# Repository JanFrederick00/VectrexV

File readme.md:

# Vectrex-V

This device can generate a vector signal that can be displayed as X/Y on an oscilloscope or vector monitor.

The DACs used are MCP4811-devices featuring a built-in voltage reference, giving a stable output with a 10-bit range.

The DACs are connected to a CH32V003 microcontroller running at 48MHz. In practice the maximum output frequency on the DACs is about 60KHz, minus the time needed for calculations.

A third output channel is provided (Z) to control the beam brightness (on/off), which eliminates faint line when "jumping" from one position to another.

A simple 2-channel pulse wave audio output is provided.

A controller header can be used to connect a SNES/NES controller or potentially other styles of controllers, provided they use no more than 3 I/O pins.

# Firmware

Firmware is written in c++ (Arduino / PlatformIO). 

## Asteroids

As a proof-of-concept I implemented my own version of the classic Atari game "Asteroids". It is not meant to be a faithful recreation of the original, even though it re-uses the graphics from the Atari version.
This program uses more than 98% of the CH32's flash memory (for game code and graphics data), and thus is probably a good representation of the capabilities of this device.

## Pong

A simple variation on a pong-like game, with (optional) gravity for the ball.

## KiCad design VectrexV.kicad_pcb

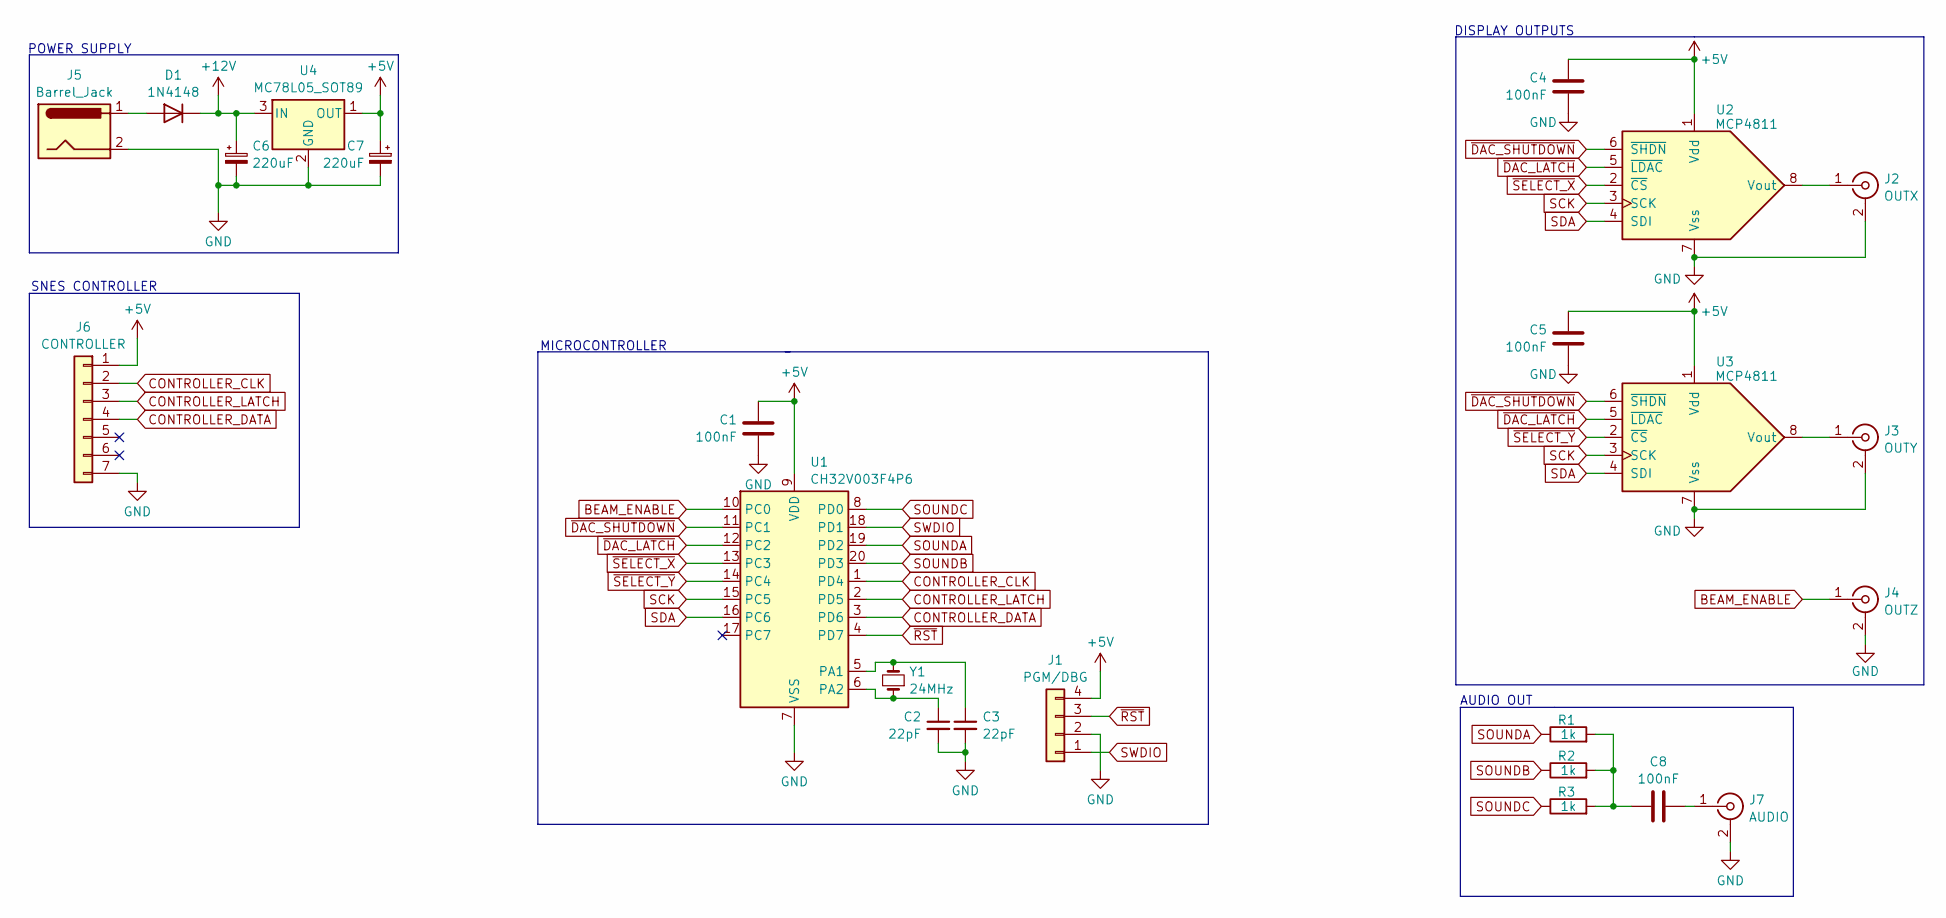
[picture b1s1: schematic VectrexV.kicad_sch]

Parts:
C1, C4, C5, C8: 100nF; C_0805_2012Metric_Pad1.18x1.45mm_HandSolder
C2, C3: 22pF; C_0805_2012Metric_Pad1.18x1.45mm_HandSolder
C6, C7: 220uF; CP_Radial_D5.0mm_P2.50mm
D1: 1N4148; D_DO-35_SOD27_P7.62mm_Horizontal
J1: PGM/DBG; PinHeader_1x04_P2.54mm_Vertical
J2: OUTX; RCA-jack
J3: OUTY; RCA-jack
J4: OUTZ; RCA-jack
J5: Barrel_Jack; BarrelJack_Horizontal
J6: CONTROLLER; PinHeader_1x07_P2.54mm_Vertical
J7: AUDIO; RCA-jack
R1, R2, R3: 1k; R_0805_2012Metric_Pad1.20x1.40mm_HandSolder
U1: CH32V003F4P6; TSSOP-20_4.4x6.5mm_P0.65mm
U2, U3: MCP4811; MSOP-8_3x3mm_P0.65mm
U4: MC78L05_SOT89; SOT-89-3
Y1: 24MHz; Crystal_HC50_Vertical

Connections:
+5V: C1.1, C4.1, C5.1, C7.1, J1.4, J6.1, U1.9 (VDD), U2.1 (Vdd), U3.1 (Vdd), U4.1 (OUT)
+12V: C6.1, D1.1 (K), U4.3 (IN)
BEAM_ENABLE: J4.1 (In), U1.10 (PC0)
CONTROLLER_CLK: J6.2, U1.1 (PD4)
CONTROLLER_DATA: J6.4, U1.3 (PD6)
CONTROLLER_LATCH: J6.3, U1.2 (PD5)
GND: C1.2, C2.2, C3.2, C4.2, C5.2, C6.2, C7.2, J1.2, J2.2 (Ext), J3.2 (Ext), J4.2 (Ext), J5.2, J6.7, J7.2 (Ext), U1.7 (VSS), U2.7 (Vss), U3.7 (Vss), U4.2 (GND)
unnamed: C8.1, R1.2, R2.2, R3.2
unnamed: D1.2 (A), J5.1
unnamed: J2.1 (In), U2.8 (Vout)
unnamed: J3.1 (In), U3.8 (Vout)
unnamed: C8.2, J7.1 (In)
unnamed: C3.1, U1.5 (PA1), Y1.2
unnamed: C2.1, U1.6 (PA2), Y1.1
SCK: U1.15 (PC5), U2.3 (SCK), U3.3 (SCK)
SDA: U1.16 (PC6), U2.4 (SDI), U3.4 (SDI)
SOUNDA: R1.1, U1.19 (PD2)
SOUNDB: R2.1, U1.20 (PD3)
SOUNDC: R3.1, U1.8 (PD0)
SWDIO: J1.1, U1.18 (PD1)
~DAC_LATCH: U1.12 (PC2), U2.5 (~LDAC), U3.5 (~LDAC)
~DAC_SHUTDOWN: U1.11 (PC1), U2.6 (~SHDN), U3.6 (~SHDN)
~RST: J1.3, U1.4 (PD7)
~SELECT_X: U1.13 (PC3), U2.2 (~CS)
~SELECT_Y: U1.14 (PC4), U3.2 (~CS)

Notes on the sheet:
POWER SUPPLY
MICROCONTROLLER
SNES CONTROLLER
AUDIO OUT
DISPLAY OUTPUTS

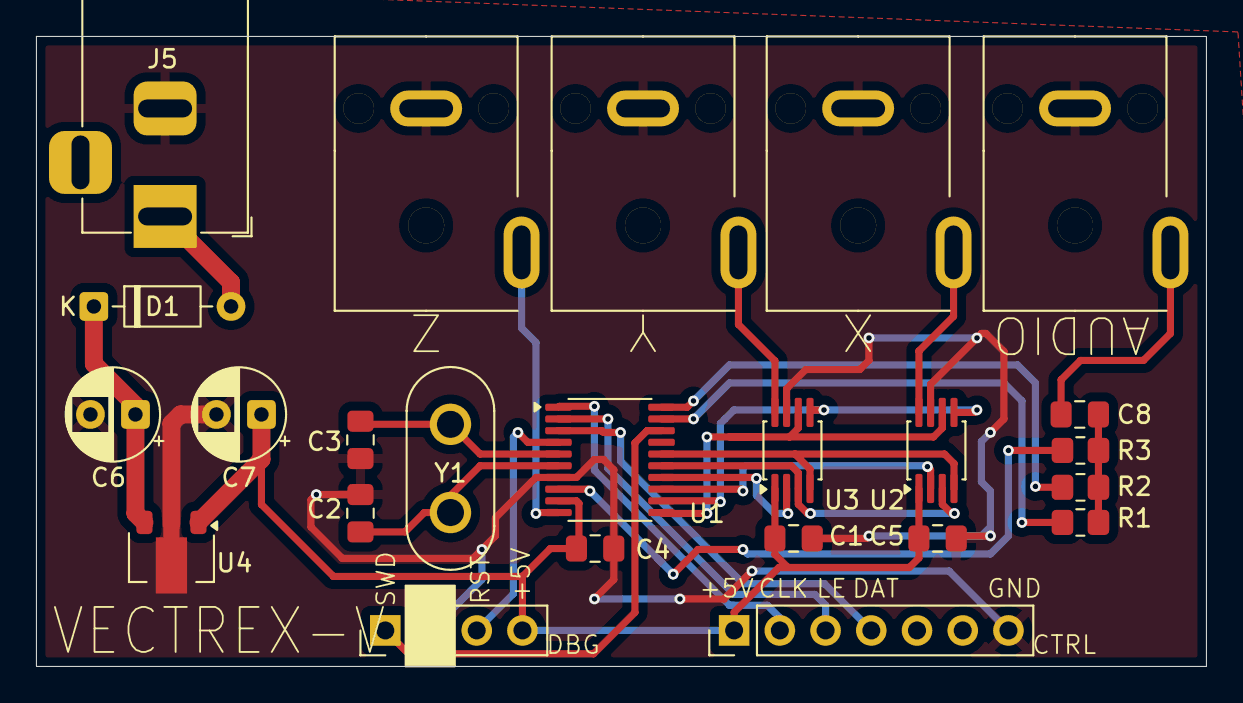
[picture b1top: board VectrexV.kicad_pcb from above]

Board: 2 copper layers, 65.0 x 35.0 mm, 24 parts (0 on the bottom side), 25 nets.

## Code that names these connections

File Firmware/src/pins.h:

#pragma once
#include <Arduino.h>

const uint8_t PIN_BRIGHTNESS = PC0;

// DACs
const uint8_t PIN_DAC_SHUTDOWN = PC1;
const uint8_t PIN_DAC_LATCH = PC2;
const uint8_t PIN_DAC_CS_X = PC3;
const uint8_t PIN_DAC_CS_Y = PC4;
const uint8_t PIN_DAC_SCK = PC5;
const uint8_t PIN_DAC_SDA = PC6;

// Sound
const uint8_t PIN_SOUNDA = PD2;
const uint8_t PIN_SOUNDB = PD3;
const uint8_t PIN_SOUNDC = PD0;

// Controller
const uint8_t PIN_CTRL_CLK = PD4;
const uint8_t PIN_CTRL_LATCH = PD5;
const uint8_t PIN_CTRL_DATA = PD6;
